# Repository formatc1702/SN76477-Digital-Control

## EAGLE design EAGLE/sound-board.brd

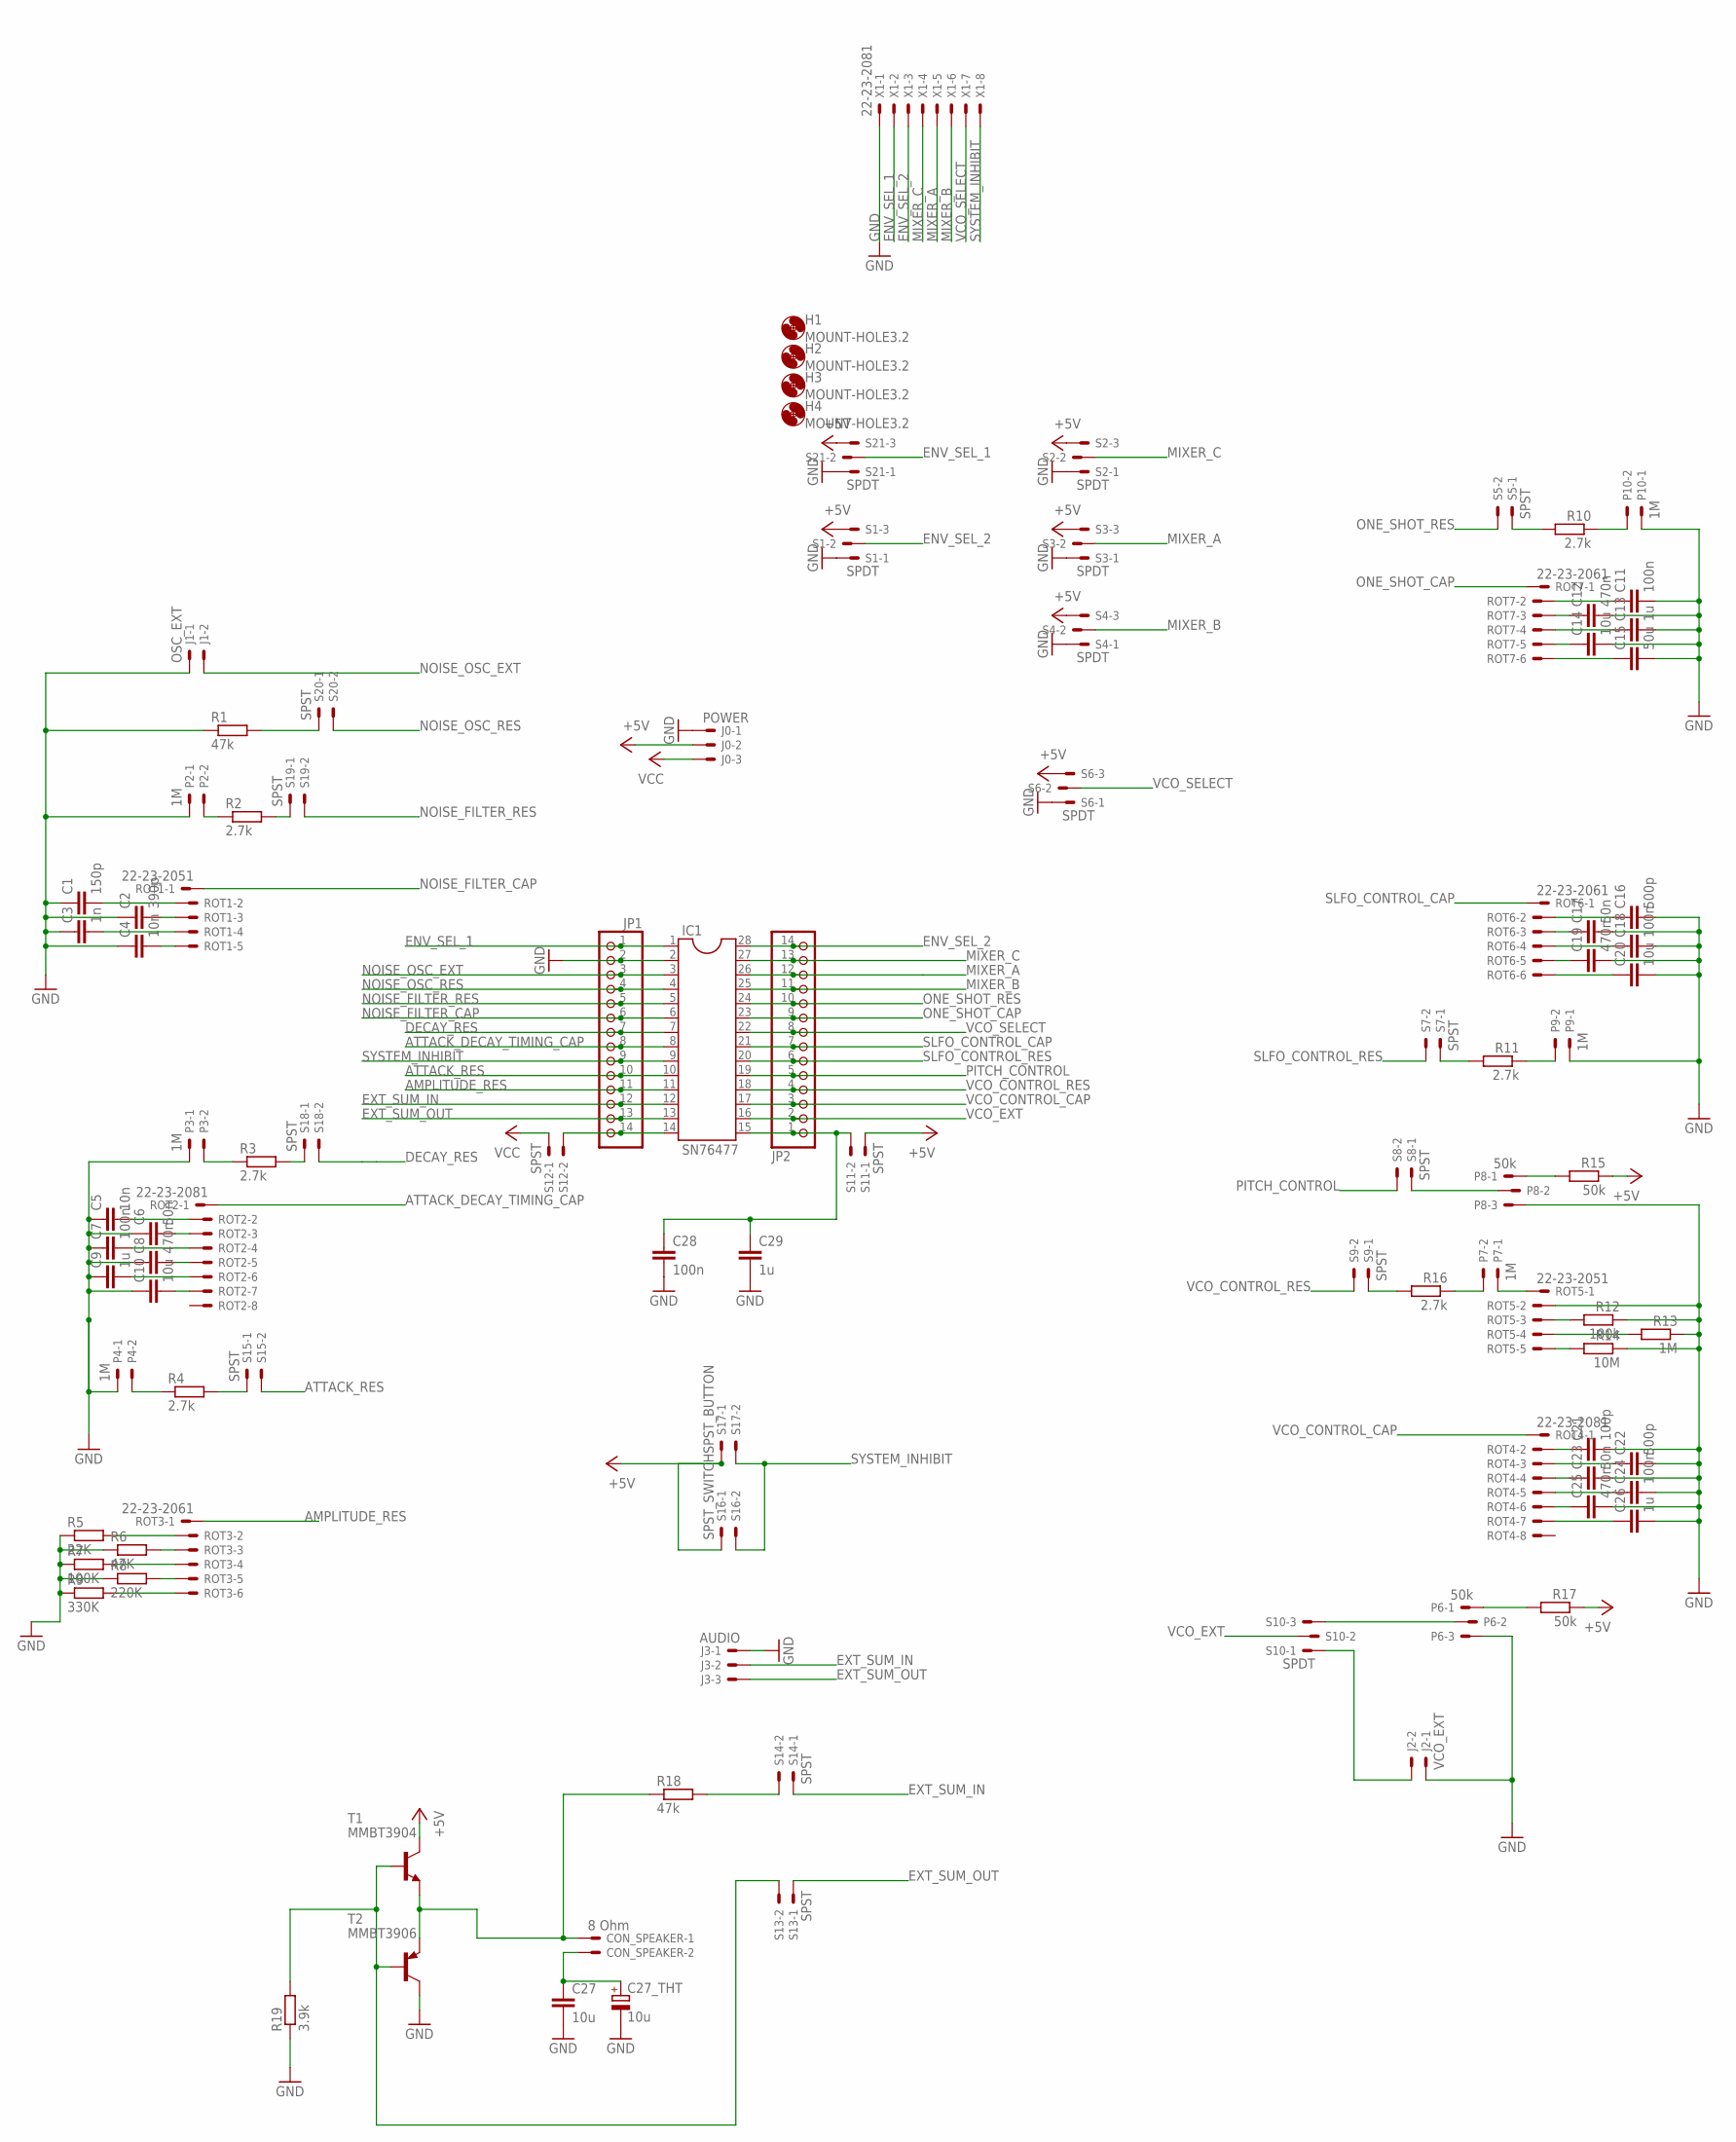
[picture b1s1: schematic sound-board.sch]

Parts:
C1: 150p; C0805
C2: 390p; C0805
C3: 1n; C0805
C4, C5: 10n; C0805
C6, C17, C23: 50n; C0805
C7, C11, C18, C24, C28: 100n; C0805
C8, C12, C19, C25: 470n; C0805
C9, C13, C26, C29: 1u; C0805
C10, C14, C20, C27: 10u; C0805
C15: 50u; C0805
C16, C22: 500p; C0805
C21: 100p; C0805
C27_THT: 10u; E2,5-5
CON_SPEAKER: 8 Ohm; 22-23-2021
H1, H2, H3, H4: MOUNT-HOLE3.2; 3,2
IC1: SN76477; DIL28-6
J0: POWER; 22-23-2031
J1: OSC_EXT; 22-23-2021
J2: VCO_EXT; 22-23-2021
J3: AUDIO; 22-23-2031
JP1, JP2: PINHD-1X14; 1X14
P2, P3, P4, P7, P9, P10: 1M; 22-23-2021
P6, P8: 50k; 22-23-2031
R1, R18: 47k; R0805
R2, R3, R4, R10, R11, R16: 2.7k; R0805
R5: 22K; R0805
R6: 47K; R0805
R7: 100K; R0805
R8: 220K; R0805
R9: 330K; R0805
R12: 100k; R0805
R13: 1M; R0805
R14: 10M; R0805
R15, R17: 50k; R0805
R19: 3.9k; R0805
ROT1, ROT5: 22-23-2051
ROT2, ROT4: 22-23-2081
ROT3, ROT6, ROT7: 22-23-2061
S1, S2, S3, S4, S6, S10, S21: SPDT; 22-23-2031
S5, S7, S8, S9, S11, S12, S13, S14, S15, S18, S19, S20: SPST; 22-23-2021
S16: SPST_SWITCH; 22-23-2021
S17: SPST_BUTTON; 22-23-2021
T1: MMBT3904; SOT23-BEC
T2: MMBT3906; SOT23-BEC
X1: 22-23-2081

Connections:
+5V: J0.2, R15.1, R17.1, S1.3, S2.3, S3.3, S4.3, S6.3, S11.1, S16.1, S17.1, S21.3, T1.C
AMPLITUDE_RES: IC1.11, JP1.11, ROT3.1
ATTACK_DECAY_TIMING_CAP: IC1.8, JP1.8, ROT2.1
ATTACK_RES: IC1.10, JP1.10, S15.2
BASE: R19.2, S13.2, T1.B, T2.B
DECAY_RES: IC1.7, JP1.7, S18.2
EMITTER: CON_SPEAKER.1, R18.1, T1.E, T2.E
ENV_SEL_1: IC1.1, JP1.1, S21.2, X1.2
ENV_SEL_2: IC1.28, JP2.14, S1.2, X1.3
EXT_SUM_IN: IC1.12, J3.2, JP1.12, S14.1
EXT_SUM_OUT: IC1.13, J3.3, JP1.13, S13.1
GND: C1.1, C2.1, C3.1, C4.1, C5.1, C6.1, C7.1, C8.1, C9.1, C10.1, C11.2, C12.2, C13.2, C14.2, C15.2, C16.2, C17.2, C18.2, C19.2, C20.2, C21.2, C22.2, C23.2, C24.2, C25.2, C26.2, C27.2, C27_THT.-, C28.2, C29.2, IC1.2, J0.1, J1.1, J2.1, J3.1, JP1.2, P2.1, P3.1, P4.1, P6.3, P8.3, P9.1, P10.1, R1.1, R5.1, R6.1, R7.1, R8.1, R9.1, R12.1, R13.1, R14.1, R19.1, ROT5.2, S1.1, S2.1, S3.1, S4.1, S6.1, S21.1, T2.C, X1.1
MIXER_A: IC1.26, JP2.12, S3.2, X1.5
MIXER_B: IC1.25, JP2.11, S4.2, X1.6
MIXER_C: IC1.27, JP2.13, S2.2, X1.4
unnamed: P10.2, R10.1
unnamed: R2.2, S19.1
unnamed: P3.2, R3.1
unnamed: P2.2, R2.1
unnamed: R1.2, S20.1
unnamed: R5.2, ROT3.2
unnamed: R6.2, ROT3.3
unnamed: R7.2, ROT3.4
unnamed: R8.2, ROT3.5
unnamed: R10.2, S5.1
unnamed: C16.1, ROT6.2
unnamed: C27.1, C27_THT.+, CON_SPEAKER.2
unnamed: IC1.14, JP1.14, S12.2
unnamed: C11.1, ROT7.2
unnamed: C13.1, ROT7.4
unnamed: C15.1, ROT7.6
unnamed: C14.1, ROT7.5
unnamed: C18.1, ROT6.4
unnamed: C20.1, ROT6.6
unnamed: P9.2, R11.1
unnamed: R12.2, ROT5.3
unnamed: R14.2, ROT5.5
unnamed: R13.2, ROT5.4
unnamed: J2.2, S10.1
unnamed: C21.1, ROT4.2
unnamed: R9.2, ROT3.6
unnamed: C1.2, ROT1.2
unnamed: C2.2, ROT1.3
unnamed: C3.2, ROT1.4
unnamed: C4.2, ROT1.5
unnamed: C5.2, ROT2.2
unnamed: C6.2, ROT2.3
unnamed: C7.2, ROT2.4
unnamed: C8.2, ROT2.5
unnamed: C9.2, ROT2.6
unnamed: C10.2, ROT2.7
unnamed: R3.2, S18.1
unnamed: P4.2, R4.1
unnamed: R4.2, S15.1
unnamed: C12.1, ROT7.3
unnamed: C19.1, ROT6.5
unnamed: C17.1, ROT6.3
unnamed: R11.2, S7.1
unnamed: C23.1, ROT4.4
unnamed: C25.1, ROT4.6
unnamed: C26.1, ROT4.7
unnamed: C24.1, ROT4.5
unnamed: C22.1, ROT4.3
unnamed: P8.2, S8.1
unnamed: P8.1, R15.2
unnamed: P7.2, R16.1
unnamed: R16.2, S9.1
unnamed: P7.1, ROT5.1
unnamed: P6.2, S10.3
unnamed: P6.1, R17.2
unnamed: R18.2, S14.2
NOISE_FILTER_CAP: IC1.6, JP1.6, ROT1.1
NOISE_FILTER_RES: IC1.5, JP1.5, S19.2
NOISE_OSC_EXT: IC1.3, J1.2, JP1.3
NOISE_OSC_RES: IC1.4, JP1.4, S20.2
ONE_SHOT_CAP: IC1.23, JP2.9, ROT7.1
ONE_SHOT_RES: IC1.24, JP2.10, S5.2
PITCH_CONTROL: IC1.19, JP2.5, S8.2
SLFO_CONTROL_CAP: IC1.21, JP2.7, ROT6.1
SLFO_CONTROL_RES: IC1.20, JP2.6, S7.2
SYSTEM_INHIBIT: IC1.9, JP1.9, S16.2, S17.2, X1.8
VCC: J0.3, S12.1
VCO_CONTROL_CAP: IC1.17, JP2.3, ROT4.1
VCO_CONTROL_RES: IC1.18, JP2.4, S9.2
VCO_EXT: IC1.16, JP2.2, S10.2
VCO_SELECT: IC1.22, JP2.8, S6.2, X1.7
VREG: C28.1, C29.1, IC1.15, JP2.1, S11.2

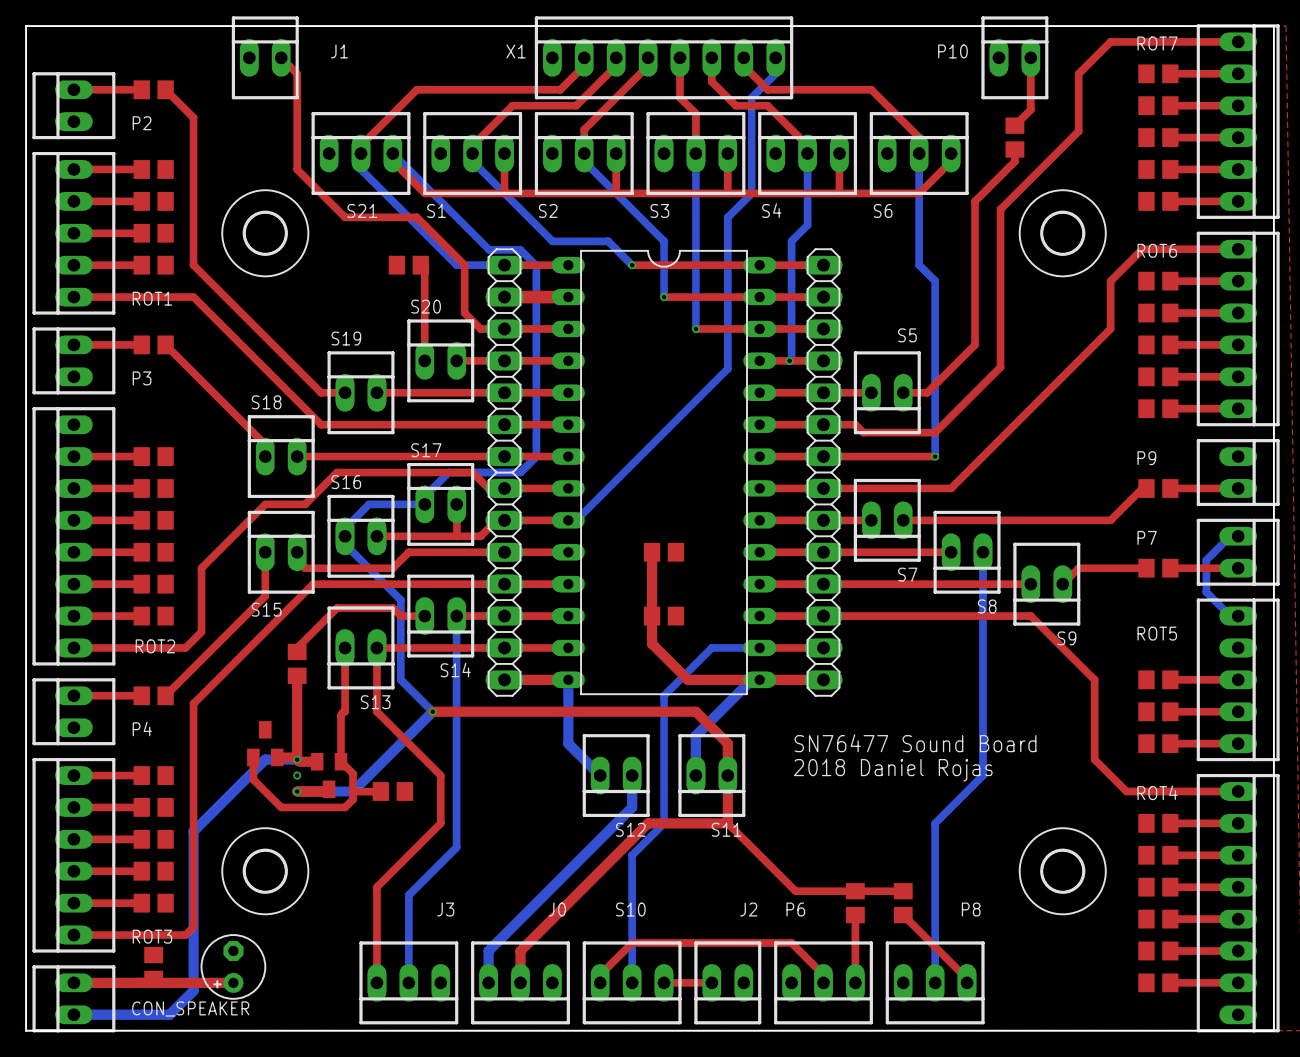
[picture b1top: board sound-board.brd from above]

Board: 2 copper layers, 99.4 x 80.0 mm, 100 parts (0 on the bottom side), 87 nets.

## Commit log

2018-03-20 Add EAGLE files for SN76477 sound board
2018-03-20 Add documentation folder
2018-03-20 Minor modifications to PCB
2018-03-21 Rearrange schematic components
